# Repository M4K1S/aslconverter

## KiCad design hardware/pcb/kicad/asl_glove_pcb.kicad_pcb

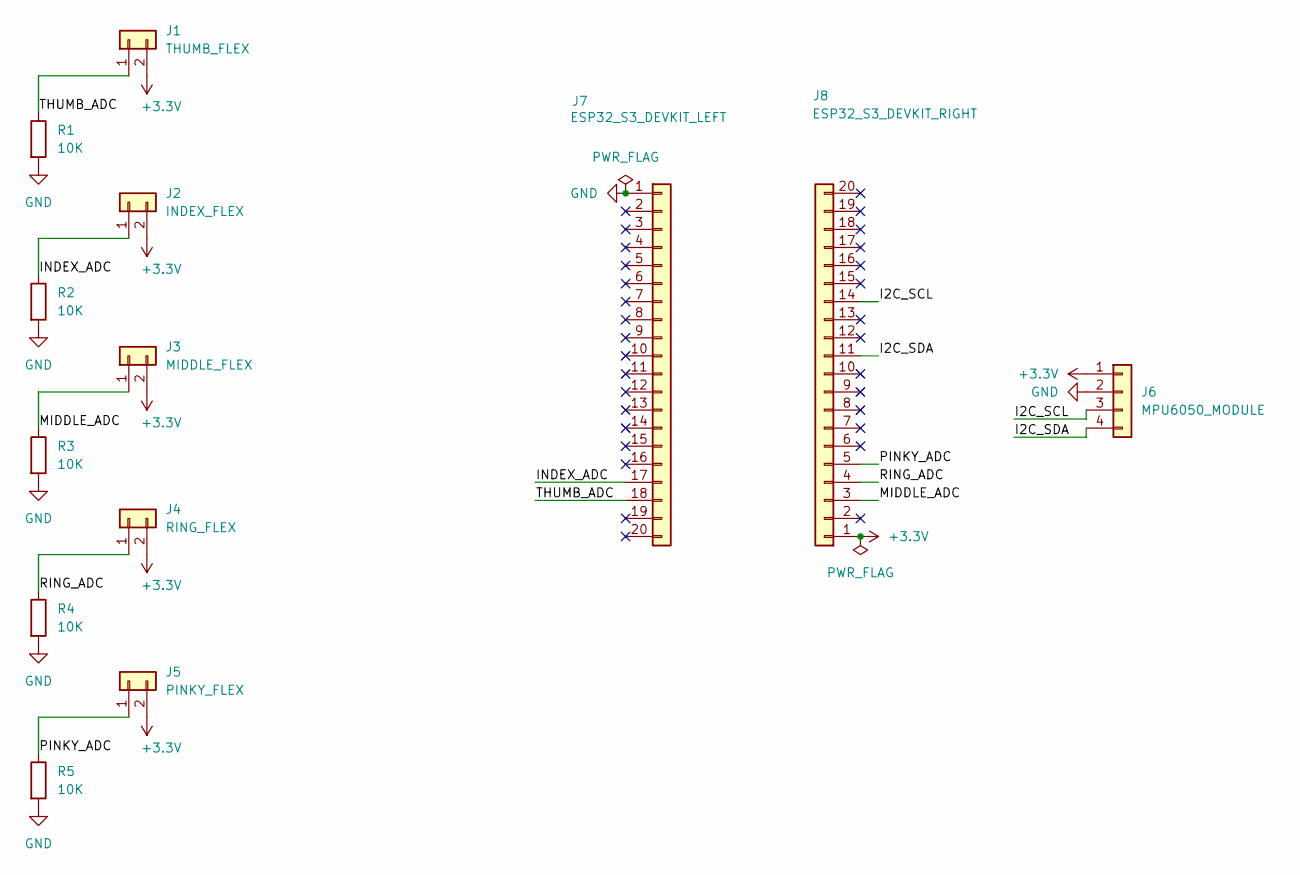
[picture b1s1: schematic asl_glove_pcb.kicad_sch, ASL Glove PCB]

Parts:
J1: THUMB_FLEX; PinHeader_1x02_P2.54mm_Vertical
J2: INDEX_FLEX; PinHeader_1x02_P2.54mm_Vertical
J3: MIDDLE_FLEX; PinHeader_1x02_P2.54mm_Vertical
J4: RING_FLEX; PinHeader_1x02_P2.54mm_Vertical
J5: PINKY_FLEX; PinHeader_1x02_P2.54mm_Vertical
J6: MPU6050_MODULE; PinHeader_1x04_P2.54mm_Vertical
J7: ESP32_S3_DEVKIT_LEFT; PinHeader_1x20_P2.54mm_Vertical
J8: ESP32_S3_DEVKIT_RIGHT; PinHeader_1x20_P2.54mm_Vertical
R1, R2, R3, R4, R5: 10K; R_Axial_DIN0207_L6.3mm_D2.5mm_P7.62mm_Horizontal

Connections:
+3.3V: J1.2, J2.2, J3.2, J4.2, J5.2, J6.1, J8.1
/I2C_SCL: J6.3, J8.14
/I2C_SDA: J6.4, J8.11
/INDEX_ADC: J2.1, J7.17, R2.1
/MIDDLE_ADC: J3.1, J8.3, R3.1
/PINKY_ADC: J5.1, J8.5, R5.1
/RING_ADC: J4.1, J8.4, R4.1
/THUMB_ADC: J1.1, J7.18, R1.1
GND: J6.2, J7.1, R1.2, R2.2, R3.2, R4.2, R5.2

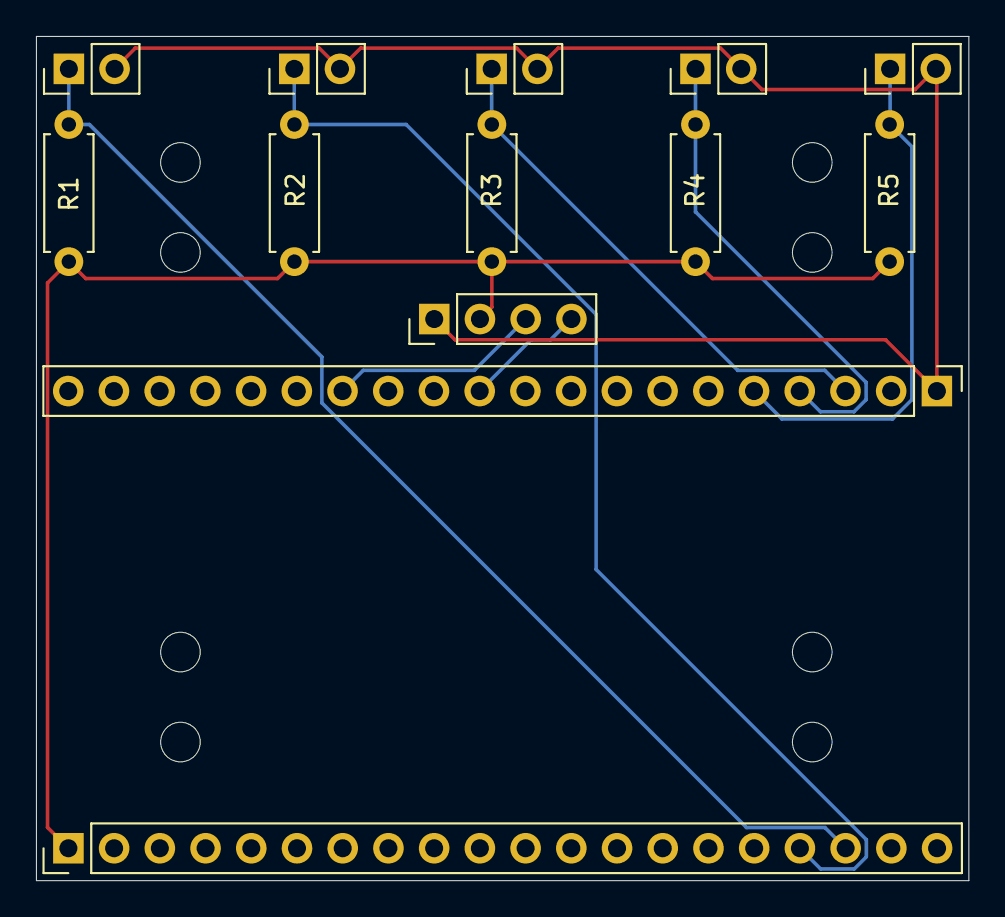
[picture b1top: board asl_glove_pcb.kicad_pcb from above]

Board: 2 copper layers, 51.8 x 46.9 mm, 13 parts (0 on the bottom side), 9 nets.
